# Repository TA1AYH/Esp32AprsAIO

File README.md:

# ESP32 APRS All in One 

Firmware v1.1 (on the kitchen)
Additions to v1.0
- Buzzer function will be active 
- You can select a friend to activate buzzer with he/she's APRS beacon
- Smart menu will be available on the screen
- up-down-ok buttons will control the smart menu

Firmware v1.0 (available)
Below functions are optional to use
- APRS Tracker with Radio TX (with GPS Module)
- APRS Tracker direct to APRS-IS with WiFi (NO Radio TX), (with GPS Module)
- APRS iGate (with Wifi connection, no need GPS module)
- APRS Digipeater ( Manually ON-OFF and if you choose it on it works Automatically if there is no internet)
- While on APRS tracker mode also you can use the module as iGate to help other stations to reach the APRS-IS server (with WiFi and GPS module)

External GPS TX & RX pins to GPS RX & TX pins of APRS AIO v1.1

Kicad design builded by TA1AYH & TA2PLT

73's

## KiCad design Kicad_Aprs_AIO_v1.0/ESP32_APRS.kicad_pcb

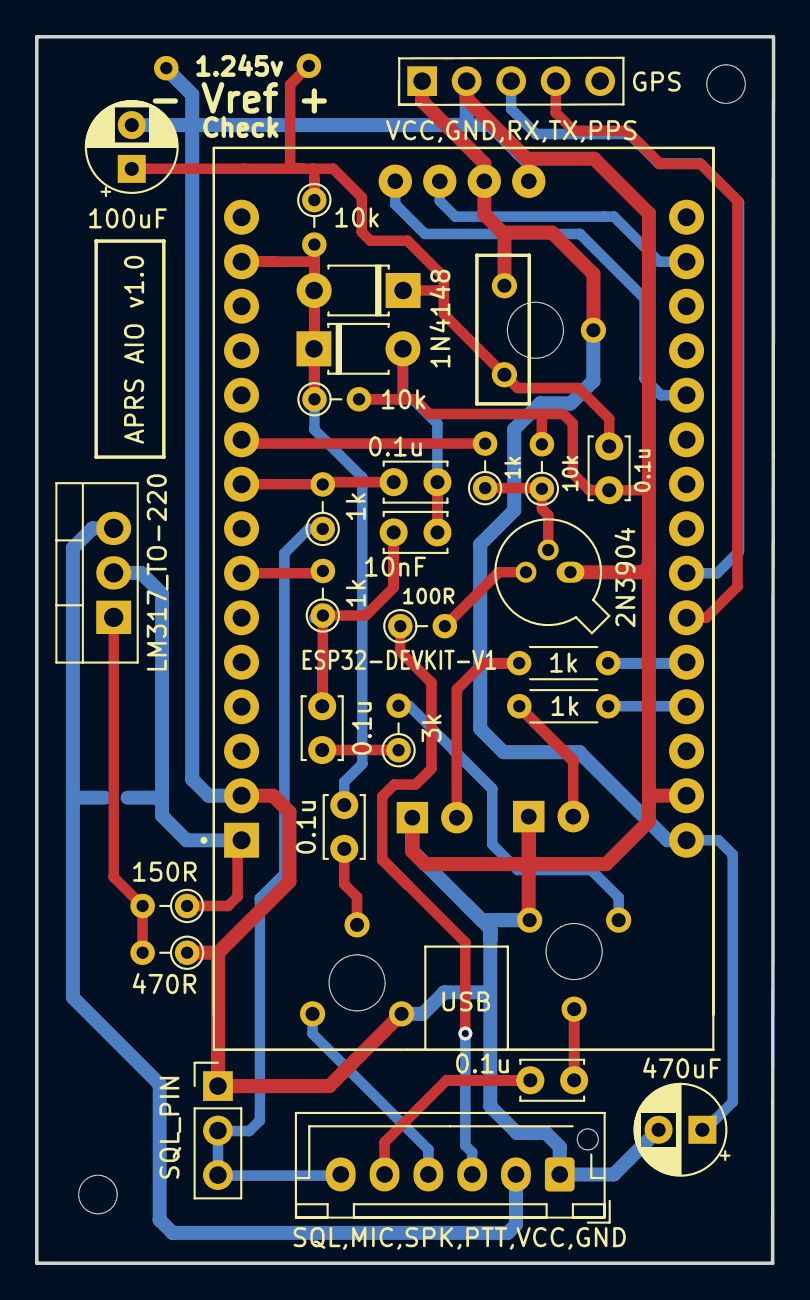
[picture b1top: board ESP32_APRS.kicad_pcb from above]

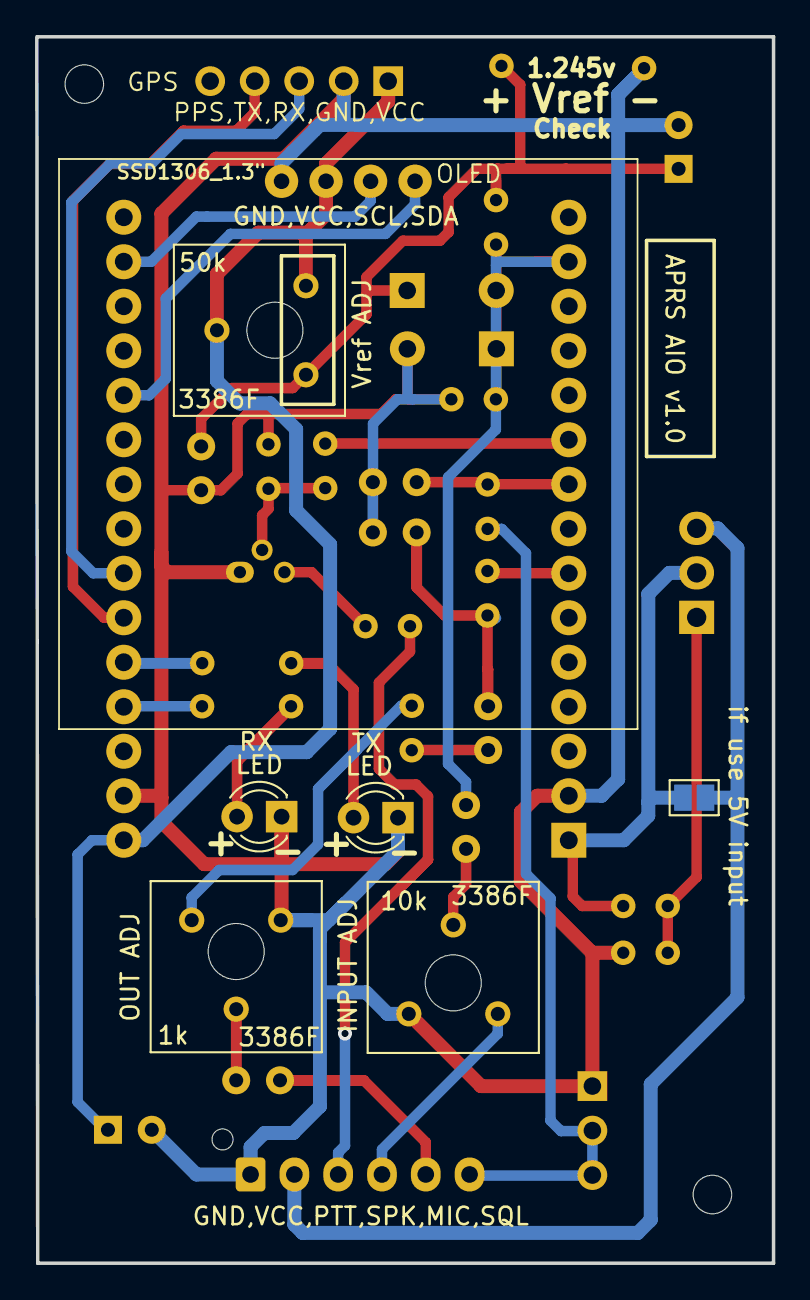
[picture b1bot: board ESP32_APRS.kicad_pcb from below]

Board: 2 copper layers, 42.1 x 70.0 mm, 35 parts (7 on the bottom side), 29 nets.

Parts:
Brd1: INPUT; JST_XH_B6B-XH-AM_1x06_P2.50mm_Vertical
Brd2: SSD1306_1.3"; OLED_SSD_1306
Brd3: GPS; PinHeader_1x05_P2.54mm_Vertical
C1, C2, C3, C4, C7: 0.1u; C_Disc_D3.4mm_W2.1mm_P2.50mm
C5: 10nF; C_Disc_D3.4mm_W2.1mm_P2.50mm
C6: 470uF; CP_Radial_D5.0mm_P2.50mm
C8: 100uF; CP_Radial_D5.0mm_P2.50mm
D1, D2: 1N4148; D_T-1_P5.08mm_Horizontal
J1: SQL_PIN; PinHeader_1x03_P2.54mm_Vertical
JP1: if use 5V input; SolderJumper-2_P1.3mm_Open_Pad1.0x1.5mm
Q1: 2N3904; TO-18-3
R1: 470R; R_Axial_DIN0204_L3.6mm_D1.6mm_P2.54mm_Vertical
R2: 100R; R_Axial_DIN0204_L3.6mm_D1.6mm_P2.54mm_Vertical
R3, R4, R7: 10k; R_Axial_DIN0204_L3.6mm_D1.6mm_P2.54mm_Vertical
R5: 150R; R_Axial_DIN0204_L3.6mm_D1.6mm_P2.54mm_Vertical
R6, R9, R10: 1k; R_Axial_DIN0204_L3.6mm_D1.6mm_P2.54mm_Vertical
R8: 3k; R_Axial_DIN0204_L3.6mm_D1.6mm_P2.54mm_Vertical
RV1: 10k; Potentiometer_Bourns_3386F_Vertical
RV2: 1k; Potentiometer_Bourns_3386F_Vertical
RV3: 50k; Potentiometer_Bourns_3386F_Vertical
RX: LED; LED_D3.0mm
RX2: 1k; R_Axial_DIN0204_L3.6mm_D1.6mm_P5.08mm_Horizontal
TX: LED; LED_D3.0mm
TX2: 1k; R_Axial_DIN0204_L3.6mm_D1.6mm_P5.08mm_Horizontal
U1: LM317_TO-220; TO-220-3_Vertical
U2: ESP32-DEVKIT-V1; ESP32_DEVKIT

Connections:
GND: Brd1.1 (GND), Brd2.1 (GND), Brd3.2 (GND), C3.2, C5.1, C6.2, C7.2, C8.2, D2.2 (A), J1.1, Q1.1 (E), R1.1, R4.2, R7.2, RV1.3, RV2.3, RX.1 (K), TX.1 (K), U2.2 (GND), U2.29 (GND)
unnamed: Brd1.2 (VCC), JP1.1 (A), U1.3 (VI)
unnamed: Brd1.3 (PTT), R2.1
unnamed: Brd1.4 (SPK), RV1.1
unnamed: Brd1.5 (MIC), C1.1
unnamed: Brd1.6 (SQL), J1.2, J1.3, R6.1
unnamed: Brd2.2 (VCC), Brd3.1 (VCC), C6.1, RV3.1, RV3.2, U2.30 (3V3)
unnamed: Brd2.3 (SCL), U2.17 (D22)
unnamed: Brd2.4 (SDA), U2.20 (D21)
unnamed: Brd3.3 (RXD), U2.24 (TX2)
unnamed: Brd3.4 (TXD), U2.25 (RX2)
unnamed: C1.2, RV2.2
unnamed: C2.1, RV1.2
unnamed: C2.2, D1.2 (A), D2.1 (K), R3.2, R4.1, U2.14 (VP)
unnamed: C3.1, R6.2, U2.9 (D33)
unnamed: C4.1, R8.1
unnamed: C4.2, C5.2, R10.1
unnamed: C7.1, C8.1, D1.1 (K), R3.1, RV3.3
unnamed: JP1.2 (B), R5.1, U1.2 (VO), U2.1 (VIN)
unnamed: Q1.2 (B), R7.1, R9.1
unnamed: Q1.3 (C), R2.2
unnamed: R1.2, R5.2, U1.1 (ADJ)
unnamed: R8.2, RV2.1
unnamed: R9.2, U2.10 (D32)
unnamed: R10.2, U2.7 (D26)
unnamed: RX.2 (A), TX2.2
unnamed: RX2.2, TX.2 (A)
unnamed: RX2.1, U2.26 (D4)
unnamed: TX2.1, U2.27 (D2)

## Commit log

2023-02-05 v.1.0
    Aprs All in One addon added
2023-06-01 README.md
